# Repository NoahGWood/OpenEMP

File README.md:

# OpenEMP

## Getting Started

### 3D Printing

3D printing files can be found in /src/3dPrint

### Schematics

Schematics were drawn in KiCAD and can be found in /src/Schematics

### Usage Information

See document [T72](t72.md)

## Purpose

The purpose of this project is to create a field-expedient small arms weapon to defeat advanced weapons systems such as tanks, APCs, radios, and other electronics-based technologies.

## Parts

The EMP consists of three parts:

1. Capacitor Bank
2. Trigger
3. Explosive Driven EMP
   * External Loop
   * Internal Loop

### Capacitor Bank

The capacitor bank supplied in this data package is single-use and designed to be affordable to mass-manufacture, relying on simple ceramic capacitors to store the seed current for the EMP. The capacitor bank consists of 72x100uF ceramic capacitors arranged in a parallel network for a total capacitance of 7,200mF which is charged externally before use via a 6-12v battery (in theory, any power source will work, including 12-24v consumer car batteries, however there is risk of damaging the board if higher voltages are used as there is NO on-board resistors to slow the charging. This is intentional to ensure the device can quickly charge up if necessary).

The capacitor bank is embedded onto a main board which houses the necessary electrical connections to utilize the device as a seed current source for the EMP. Due to the conflict in Ukraine and potential use for this device in the region, silkscreen markings have been translated into the Ukrainian language to allow insurgents fighting against Russian armor to make better use of the the device:

### Trigger

A trigger mechanism has not been included in this data-package. Instead, THT pads located at the top right of the device are utilized to allow for field-expedient "jerry-rigging" of any electronic or mechanical firing mechanism that can be derived:

One suggested triggering device is a mercury trigger or 'tilt' sensor with the detonator wired in series with the loop generator. Suitably propped up against a road or hidden under the chassis/tracks of stopped tanks for sabotage purposes would make these devices very inexpensive IEDs and anti-tank mines. The cost is only a few dollars more than a standard M67 hand-grenade with the added benefit of actually being able to disable a tank at such a low cost.

Other typical detonation sensors may be used allowing these devices to be utilized like clusterbombs dropped from aircraft onto the Russian convoys. The physical damage caused will be minimal compared to conventional (albeit more expensive) munitions, but this may be desirable for temporarily blocking bridges and roads without completely destroying that infrastructure enabling you to at a later time tow the vehicles away.

### Explosively Driven EMP

The EMP design included is based off of MIT's loop generator which is expected to produce a maximum of 36 T of flux. The EMP itself consists of a copper shell to which connects with the capacitor bank "seed source". A secondary copper pipe held in-place by a plastic retainer and filled with C-4 high-explosives completes EMP as shown in the MIT documentation:

The external loop can be fabricated by off-the-shelf 4" copper pipe while the inner loop consists of an off-the-shelf 2.5" copper pipe both pipes cut to 2" in length.

Electronics within 3 feet (1 meter) of the EMP are expected to be severely damaged or destroyed while electronics further than 10 feet (3 meters) are expected to have minimal interference. The device itself contains 0.16kg of C-4 which will cause fatal injuries to persons within 3 feet of the device at time of detonation, with eardrum rupture from the blast at distances of 10 feet or less. The EMP grenade itself is roughly equivalent to a standard issued M67 grenade in terms of explosive force with the added risk (or benefit) of the molten copper in lieu of fragmentation.

**Individuals using this EMP should take the same/similar precautions with this device as they would any typical grenade as well as ensuring that their own electronics equipment remains outside of the flux radius of the device.**

### Retainer

An alternative retainer design to the one developed by MIT is included and can be readily 3D printed with an estimated print time of 10 minutes per retainer with 20% infill.

## Construction

### Recommended Equipment

The recommended equipment for building these devices is as follows:

1. A 3D printer which can print with 0.4mm layer resolution or better.
2. Computer system with 3D printer slicer program
3. Large diameter pipe cutters 
4. Small diameter pipe cutters

If intending to make the PCB boards as well, you will also require:

5. Laser printer with toner (for PCB masks)
6. Drill press
7. Drill-bits (0.4mm, 1mm, 1.2mm, and 6.1mm)
8. Electro-plating equipment
9. 16 needles with diameter < 0.4mm
10. SMD work station

### Required Materials

1. 1 x 4" diameter copper plumbing pipe 2" long (102mm x 51mm)
2. 1 x 2.5" diameter copper plumbing pipe 2" long (65mm x 51mm)
3. 1 x 3D printed retainer (approx. 4-10g plastic filament)
4. 1 x Capacitor Bank Board
5. 0.16Kg C-4 High Explosive (or similar)
6. Detonator & Trigger Mechanism

If building the PCB board as well, you will also require:

1. 2 x 80mm x 50mm PCB boards
2. Toner transfer paper
3. 1 x PCB etching kit
4. 73 x 1206 SMD Capacitors @ 100uF
5. Solder & Flux

### Cost Estimate (Rough)

| Item                  | Qty  | Cost Per    | Subtotal |
| --------------------- | ---- | ----------- | -------- |
| 4" x 2" copper pipe   | 1    | $11.27      | $11.27   |
| 2.5" x 2" copper pipe | 1    | $4.17       | $4.17    |
| Capacitor Bank Board  | 1    | $8          | $8       |
| C-4 Explosives        | 1    | $21.17      | $21.17   |
| Plastic Filament      | 1    | $0.01       | $0.01    |
|                       |      | Total Cost: | $44.62   |

## See Also

https://dspace.mit.edu/handle/1721.1/129899

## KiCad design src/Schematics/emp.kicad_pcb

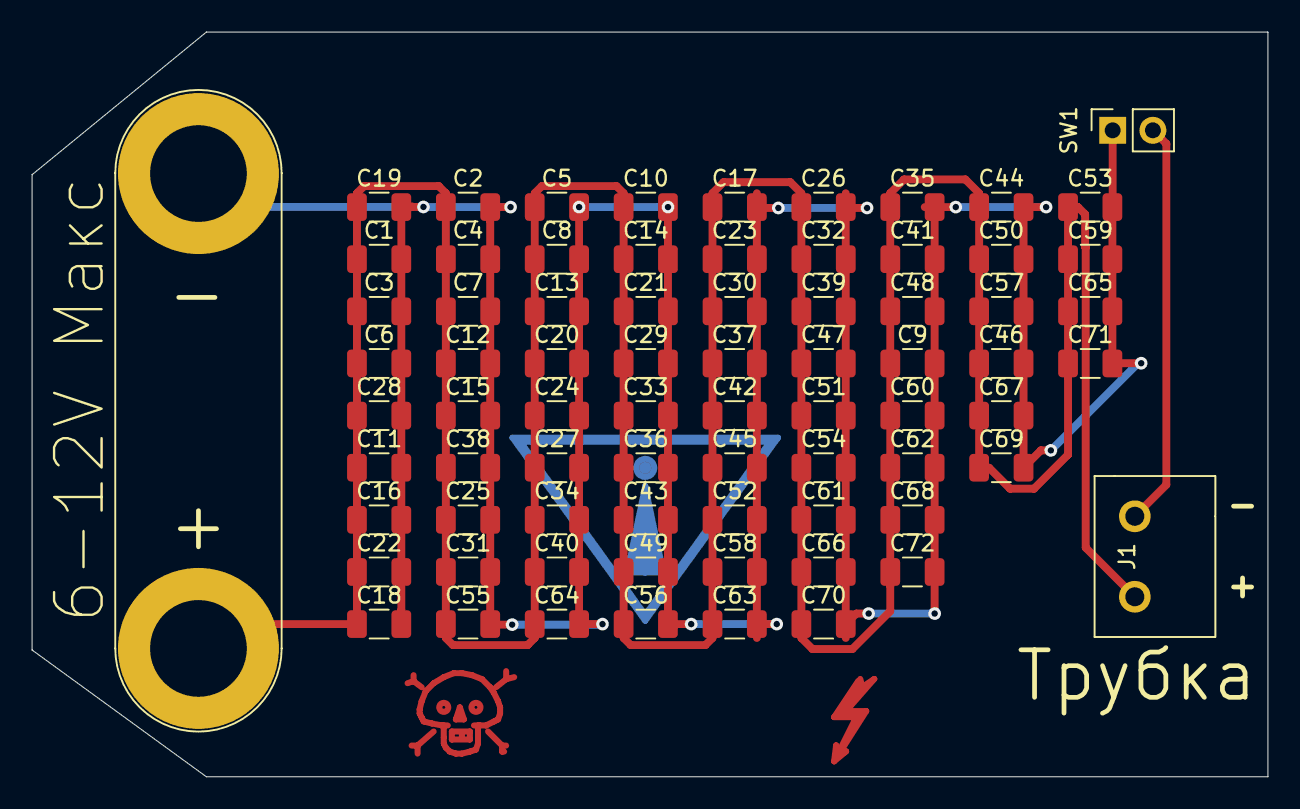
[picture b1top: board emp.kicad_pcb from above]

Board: 2 copper layers, 78.0 x 47.0 mm, 75 parts (0 on the bottom side), 3 nets.

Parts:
BT1: 9v; Banana_Jack_2Pin
C1, C2, C3, C4, C5, C6, C7, C8, C9, C10, C11, C12, C13, C14, C15, C16, C17, C18, C19, C20, C21, C22, C23, C24, C25, C26, C27, C28, C29, C30, C31, C32, C33, C34, C35, C36, C37, C38, C39, C40, C41, C42, C43, C44, C45, C46, C47, C48, C49, C50, C51, C52, C53, C54, C55, C56, C57, C58, C59, C60, C61, C62, C63, C64, C65, C66, C67, C68, C69, C70, C71, C72: 100uF; C_1206_3216Metric
J1: x; screw_terminal_02
SW1: DET; PinSocket_1x02_P2.54mm_Vertical

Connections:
+: BT1.1, C1.1, C2.1, C3.1, C4.1, C5.1, C6.1, C7.1, C8.1, C9.1, C10.1, C11.1, C12.1, C13.1, C14.1, C15.1, C16.1, C17.1, C18.1, C19.1, C20.1, C21.1, C22.1, C23.1, C24.1, C25.1, C26.1, C27.1, C28.1, C29.1, C30.1, C31.1, C32.1, C33.1, C34.1, C35.1, C36.1, C37.1, C38.1, C39.1, C40.1, C41.1, C42.1, C43.1, C44.1, C45.1, C46.1, C47.1, C48.1, C49.1, C50.1, C51.1, C52.1, C53.1, C54.1, C55.1, C56.1, C57.1, C58.1, C59.1, C60.1, C61.1, C62.1, C63.1, C64.1, C65.1, C66.1, C67.1, C68.1, C69.1, C70.1, C71.1, C72.1, J1.2
-: BT1.2, C1.2, C2.2, C3.2, C4.2, C5.2, C6.2, C7.2, C8.2, C9.2, C10.2, C11.2, C12.2, C13.2, C14.2, C15.2, C16.2, C17.2, C18.2, C19.2, C20.2, C21.2, C22.2, C23.2, C24.2, C25.2, C26.2, C27.2, C28.2, C29.2, C30.2, C31.2, C32.2, C33.2, C34.2, C35.2, C36.2, C37.2, C38.2, C39.2, C40.2, C41.2, C42.2, C43.2, C44.2, C45.2, C46.2, C47.2, C48.2, C49.2, C50.2, C51.2, C52.2, C53.2, C54.2, C55.2, C56.2, C57.2, C58.2, C59.2, C60.2, C61.2, C62.2, C63.2, C64.2, C65.2, C66.2, C67.2, C68.2, C69.2, C70.2, C71.2, C72.2, SW1.1
unnamed: J1.1, SW1.2

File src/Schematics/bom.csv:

Designator, Value,Footprint,JLCPCB Part #
J1,x,custom:screw_terminal_02,C474881
C1,100uF,Capacitor_SMD:C_1206_3216Metric,C15008
C5,100uF,Capacitor_SMD:C_1206_3216Metric,C15008
C9,100uF,Capacitor_SMD:C_1206_3216Metric,C15008
C13,100uF,Capacitor_SMD:C_1206_3216Metric,C15008
C17,100uF,Capacitor_SMD:C_1206_3216Metric,C15008
C21,100uF,Capacitor_SMD:C_1206_3216Metric,C15008
C25,100uF,Capacitor_SMD:C_1206_3216Metric,C15008
C29,100uF,Capacitor_SMD:C_1206_3216Metric,C15008
C33,100uF,Capacitor_SMD:C_1206_3216Metric,C15008
C37,100uF,Capacitor_SMD:C_1206_3216Metric,C15008
C41,100uF,Capacitor_SMD:C_1206_3216Metric,C15008
C45,100uF,Capacitor_SMD:C_1206_3216Metric,C15008
C49,100uF,Capacitor_SMD:C_1206_3216Metric,C15008
C53,100uF,Capacitor_SMD:C_1206_3216Metric,C15008
C57,100uF,Capacitor_SMD:C_1206_3216Metric,C15008
C61,100uF,Capacitor_SMD:C_1206_3216Metric,C15008
C65,100uF,Capacitor_SMD:C_1206_3216Metric,C15008
C69,100uF,Capacitor_SMD:C_1206_3216Metric,C15008
C50,100uF,Capacitor_SMD:C_1206_3216Metric,C15008
C54,100uF,Capacitor_SMD:C_1206_3216Metric,C15008
C58,100uF,Capacitor_SMD:C_1206_3216Metric,C15008
C62,100uF,Capacitor_SMD:C_1206_3216Metric,C15008
C66,100uF,Capacitor_SMD:C_1206_3216Metric,C15008
C70,100uF,Capacitor_SMD:C_1206_3216Metric,C15008
C26,100uF,Capacitor_SMD:C_1206_3216Metric,C15008
C30,100uF,Capacitor_SMD:C_1206_3216Metric,C15008
C34,100uF,Capacitor_SMD:C_1206_3216Metric,C15008
C38,100uF,Capacitor_SMD:C_1206_3216Metric,C15008
C42,100uF,Capacitor_SMD:C_1206_3216Metric,C15008
C46,100uF,Capacitor_SMD:C_1206_3216Metric,C15008
C2,100uF,Capacitor_SMD:C_1206_3216Metric,C15008
C6,100uF,Capacitor_SMD:C_1206_3216Metric,C15008
C10,100uF,Capacitor_SMD:C_1206_3216Metric,C15008
C14,100uF,Capacitor_SMD:C_1206_3216Metric,C15008
C18,100uF,Capacitor_SMD:C_1206_3216Metric,C15008
C22,100uF,Capacitor_SMD:C_1206_3216Metric,C15008
C3,100uF,Capacitor_SMD:C_1206_3216Metric,C15008
C7,100uF,Capacitor_SMD:C_1206_3216Metric,C15008
C11,100uF,Capacitor_SMD:C_1206_3216Metric,C15008
C15,100uF,Capacitor_SMD:C_1206_3216Metric,C15008
C19,100uF,Capacitor_SMD:C_1206_3216Metric,C15008
C23,100uF,Capacitor_SMD:C_1206_3216Metric,C15008
C27,100uF,Capacitor_SMD:C_1206_3216Metric,C15008
C31,100uF,Capacitor_SMD:C_1206_3216Metric,C15008
C35,100uF,Capacitor_SMD:C_1206_3216Metric,C15008
C39,100uF,Capacitor_SMD:C_1206_3216Metric,C15008
C43,100uF,Capacitor_SMD:C_1206_3216Metric,C15008
C47,100uF,Capacitor_SMD:C_1206_3216Metric,C15008
C51,100uF,Capacitor_SMD:C_1206_3216Metric,C15008
C55,100uF,Capacitor_SMD:C_1206_3216Metric,C15008
C59,100uF,Capacitor_SMD:C_1206_3216Metric,C15008
C63,100uF,Capacitor_SMD:C_1206_3216Metric,C15008
C67,100uF,Capacitor_SMD:C_1206_3216Metric,C15008
C71,100uF,Capacitor_SMD:C_1206_3216Metric,C15008
C52,100uF,Capacitor_SMD:C_1206_3216Metric,C15008
C56,100uF,Capacitor_SMD:C_1206_3216Metric,C15008
C60,100uF,Capacitor_SMD:C_1206_3216Metric,C15008
C64,100uF,Capacitor_SMD:C_1206_3216Metric,C15008
C68,100uF,Capacitor_SMD:C_1206_3216Metric,C15008
C72,100uF,Capacitor_SMD:C_1206_3216Metric,C15008
C28,100uF,Capacitor_SMD:C_1206_3216Metric,C15008
C32,100uF,Capacitor_SMD:C_1206_3216Metric,C15008
C36,100uF,Capacitor_SMD:C_1206_3216Metric,C15008
C40,100uF,Capacitor_SMD:C_1206_3216Metric,C15008
C44,100uF,Capacitor_SMD:C_1206_3216Metric,C15008
C48,100uF,Capacitor_SMD:C_1206_3216Metric,C15008
C4,100uF,Capacitor_SMD:C_1206_3216Metric,C15008
C8,100uF,Capacitor_SMD:C_1206_3216Metric,C15008
C12,100uF,Capacitor_SMD:C_1206_3216Metric,C15008
C16,100uF,Capacitor_SMD:C_1206_3216Metric,C15008
C20,100uF,Capacitor_SMD:C_1206_3216Metric,C15008
C24,100uF,Capacitor_SMD:C_1206_3216Metric,C15008

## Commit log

2022-03-12 modified: README.md new file: imgs/1g46.jpg new file: imgs/9m119.png new file: imgs/back_borad.png new file: imgs/emp_loop.png new file: imgs/fine.jpg new file: imgs/front_board.png new file: imgs/me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
